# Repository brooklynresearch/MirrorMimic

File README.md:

# Mirror Mimic

This repository is for communicating and controlling robotic systems.
Currently set up for controlling torso, neck, and upper arm articulation.

## Software
1. [Arduino 1.6.8](https://www.arduino.cc)
2. [Teensyduino](https://www.pjrc.com/teensy/teensyduino.html)

### Software Libraries/Dependencies
1. DynamixelController - Controlling Dynamixels with the Teensy (Based on Arbotix Library)
2. [OSC - OSC communication with the Teensy](https://github.com/CNMAT/OSC)

## Hardware
1. [Microcontroller - Teensy 3.2](https://www.pjrc.com/store/teensy32.html)
2. [Servo - Dynamixel MX-64T](http://www.trossenrobotics.com/p/mx-64t-dynamixel-robot-actuator.aspx)
3. [Stepper Motor NEMA23 - 23L310S-LW8](http://www.anaheimautomation.com/products/stepper/stepper-motor-item.php?sID=20&pt=i&tID=75&cID=19)
4. [Stepper Driver - MBC25081TB](http://www.anaheimautomation.com/products/stepper/stepper-driver-item.php?sID=56&serID=4&pt=i&tID=87&cID=20)

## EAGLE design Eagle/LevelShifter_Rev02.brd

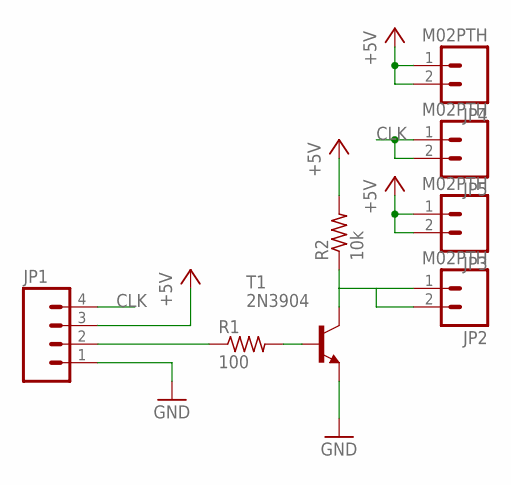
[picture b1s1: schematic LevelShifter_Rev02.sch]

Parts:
JP1: M04SCREW; SCREWTERMINAL-3.5MM-4
JP2, JP3, JP4, JP5: M02PTH; 1X02
R1: 100; 0204/7
R2: 10k; 0204/7
T1: 2N3904; TO92

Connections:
+5V: JP1.3, JP3.1, JP3.2, JP4.1, JP4.2, R2.2
CLK: JP1.4, JP5.1, JP5.2
GND: JP1.1, T1.3 (E)
unnamed: R1.2, T1.2 (B)
unnamed: JP2.1, JP2.2, R2.1, T1.1 (C)
unnamed: JP1.2, R1.1

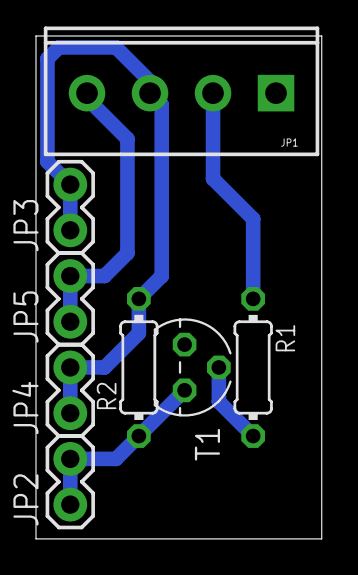
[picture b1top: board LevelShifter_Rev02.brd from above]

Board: 2 copper layers, 15.9 x 27.9 mm, 8 parts (0 on the bottom side), 6 nets.

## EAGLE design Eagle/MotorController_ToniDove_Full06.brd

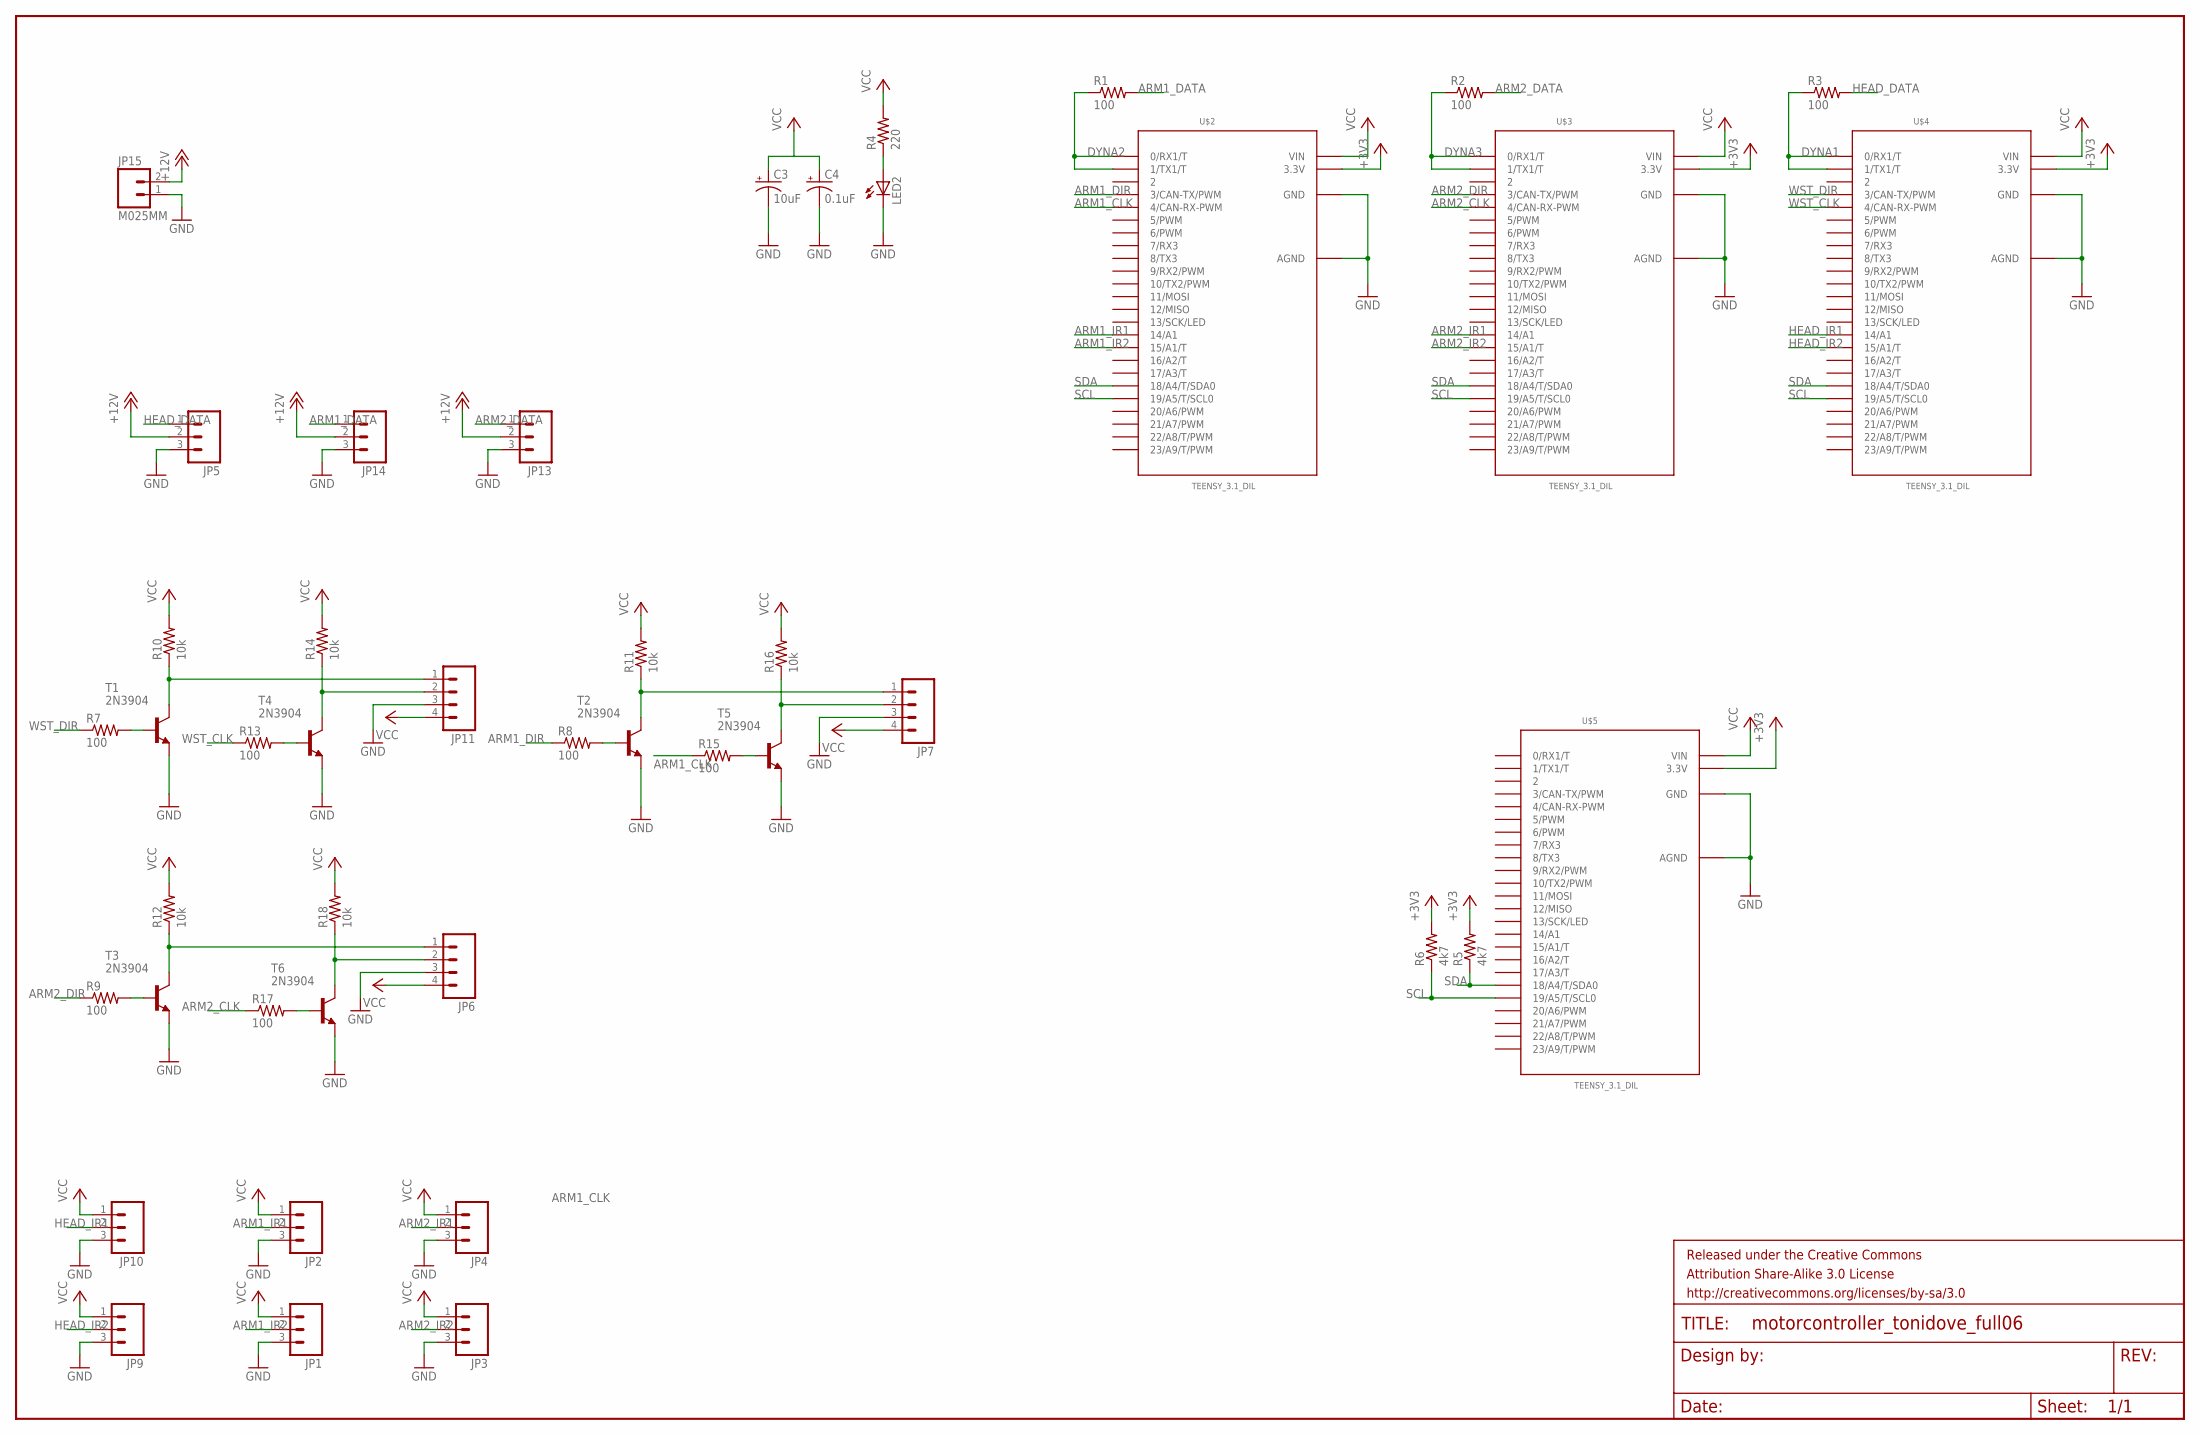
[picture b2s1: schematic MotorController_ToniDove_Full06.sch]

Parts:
C3: 10uF; E2,5-6E
C4: 0.1uF; E2,5-6E
FRAME1: FRAME-LEDGER; CREATIVE_COMMONS
JP1, JP2, JP3, JP4, JP5, JP9, JP10, JP13, JP14: M03PTH; 1X03
JP6, JP7, JP11: M04SCREW; SCREWTERMINAL-3.5MM-4
JP15: M025MM; SCREWTERMINAL-5MM-2
LED2: LED5MM
R1, R2, R3, R7, R8, R9, R13, R15, R17: 100; 0204/7
R4: 220; 0204/7
R5, R6: 4k7; 0204/7
R10, R11, R12, R14, R16, R18: 10k; 0204/7
T1, T2, T3, T4, T5, T6: 2N3904; TO92
U$2, U$3, U$4, U$5: TEENSY_3.1_DIL; TEENSY3-DIL

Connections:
+3V3: R5.2, R6.2, U$2.3.3V, U$3.3.3V, U$4.3.3V, U$5.3.3V
+12V: JP5.2, JP13.2, JP14.2, JP15.2
ARM1_CLK: R15.1, U$2.4 (4/CAN-RX-PWM)
ARM1_DATA: JP14.1, R1.2
ARM1_DIR: R8.1, U$2.3 (3/CAN-TX/PWM)
ARM1_IR1: JP2.2, U$2.14/A0 (14/A1)
ARM1_IR2: JP1.2, U$2.15/A1 (15/A1/T)
ARM2_CLK: R17.1, U$3.4 (4/CAN-RX-PWM)
ARM2_DATA: JP13.1, R2.2
ARM2_DIR: R9.1, U$3.3 (3/CAN-TX/PWM)
ARM2_IR1: JP4.2, U$3.14/A0 (14/A1)
ARM2_IR2: JP3.2, U$3.15/A1 (15/A1/T)
DYNA1: R3.1, U$4.0 (0/RX1/T), U$4.1 (1/TX1/T)
DYNA2: R1.1, U$2.0 (0/RX1/T), U$2.1 (1/TX1/T)
DYNA3: R2.1, U$3.0 (0/RX1/T), U$3.1 (1/TX1/T)
GND: C3.-, C4.-, JP1.3, JP2.3, JP3.3, JP4.3, JP5.3, JP6.3, JP7.3, JP9.3, JP10.3, JP11.3, JP13.3, JP14.3, JP15.1, LED2.K (C), T1.3 (E), T2.3 (E), T3.3 (E), T4.3 (E), T5.3 (E), T6.3 (E), U$2.AGND, U$2.GND, U$3.AGND, U$3.GND, U$4.AGND, U$4.GND, U$5.AGND, U$5.GND
HEAD_DATA: JP5.1, R3.2
HEAD_IR1: JP10.2, U$4.14/A0 (14/A1)
HEAD_IR2: JP9.2, U$4.15/A1 (15/A1/T)
unnamed: LED2.A, R4.1
unnamed: R13.2, T4.2 (B)
unnamed: R7.2, T1.2 (B)
unnamed: R8.2, T2.2 (B)
unnamed: R9.2, T3.2 (B)
unnamed: JP11.1, R10.1, T1.1 (C)
unnamed: JP7.1, R11.1, T2.1 (C)
unnamed: JP6.1, R12.1, T3.1 (C)
unnamed: JP11.2, R14.1, T4.1 (C)
unnamed: R15.2, T5.2 (B)
unnamed: JP7.2, R16.1, T5.1 (C)
unnamed: R17.2, T6.2 (B)
unnamed: JP6.2, R18.1, T6.1 (C)
SCL: R6.1, U$2.19/A5 (19/A5/T/SCL0), U$3.19/A5 (19/A5/T/SCL0), U$4.19/A5 (19/A5/T/SCL0), U$5.19/A5 (19/A5/T/SCL0)
SDA: R5.1, U$2.18/A4 (18/A4/T/SDA0), U$3.18/A4 (18/A4/T/SDA0), U$4.18/A4 (18/A4/T/SDA0), U$5.18/A4 (18/A4/T/SDA0)
VCC: C3.+, C4.+, JP1.1, JP2.1, JP3.1, JP4.1, JP6.4, JP7.4, JP9.1, JP10.1, JP11.4, R4.2, R10.2, R11.2, R12.2, R14.2, R16.2, R18.2, U$2.VIN, U$3.VIN, U$4.VIN, U$5.VIN
WST_CLK: R13.1, U$4.4 (4/CAN-RX-PWM)
WST_DIR: R7.1, U$4.3 (3/CAN-TX/PWM)

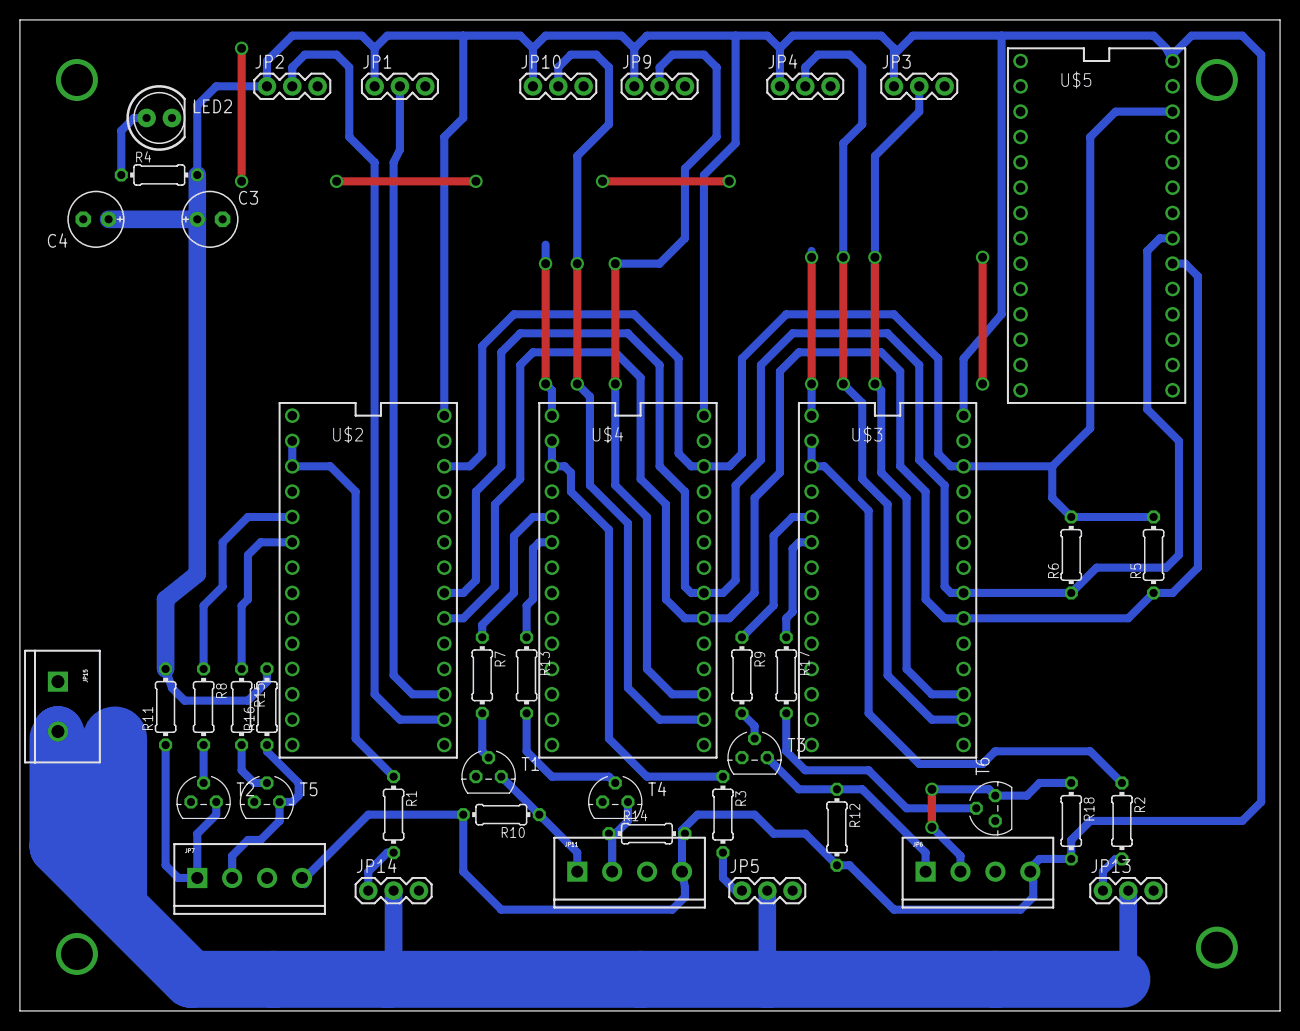
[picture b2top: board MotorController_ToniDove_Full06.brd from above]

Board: 2 copper layers, 126.3 x 99.4 mm, 45 parts (0 on the bottom side), 37 nets.

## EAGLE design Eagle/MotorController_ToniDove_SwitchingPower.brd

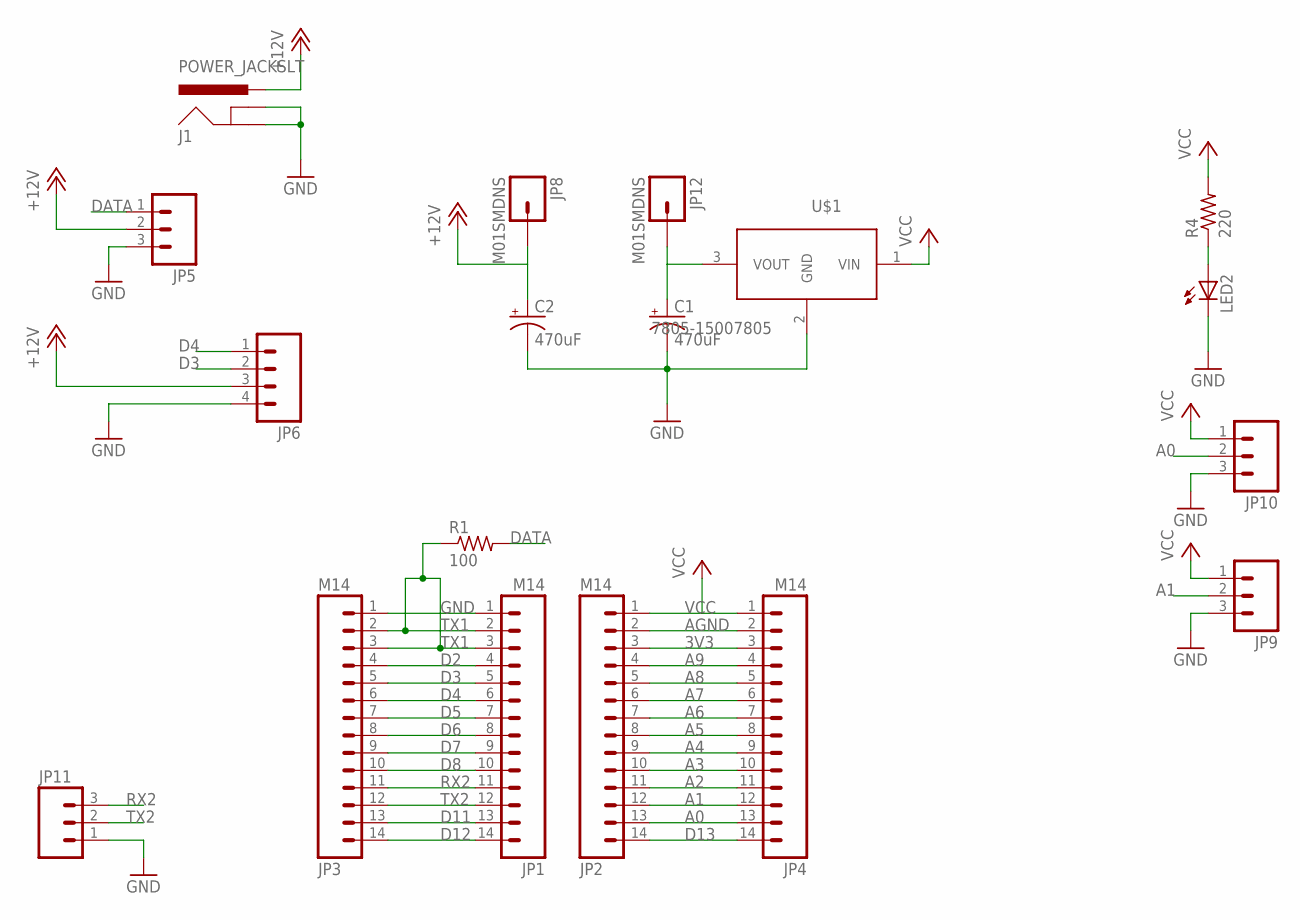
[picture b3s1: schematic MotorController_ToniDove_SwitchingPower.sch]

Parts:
C1, C2: 470uF; E5-13
J1: POWER_JACKSLT; POWER_JACK_SLOT
JP1, JP2, JP3, JP4: M14; 1X14
JP5, JP9, JP10, JP11: M03PTH; 1X03
JP6: M04PTH; 1X04
JP8, JP12: M01SMDNS; 1X01NS
LED2: LED5MM
R1: 100; 0204/7
R4: 220; 0204/7
U$1: 7805-15007805; UL94-V0

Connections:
3V3: JP2.3, JP4.3
+12V: C2.+, J1.PWR, JP5.2, JP6.3, JP8.1
A0: JP2.13, JP4.13, JP10.2
A1: JP2.12, JP4.12, JP9.2
A2: JP2.11, JP4.11
A3: JP2.10, JP4.10
A4: JP2.9, JP4.9
A5: JP2.8, JP4.8
A6: JP2.7, JP4.7
A7: JP2.6, JP4.6
A8: JP2.5, JP4.5
A9: JP2.4, JP4.4
AGND: JP2.2, JP4.2
D2: JP1.4, JP3.4
D3: JP1.5, JP3.5, JP6.2
D4: JP1.6, JP3.6, JP6.1
D5: JP1.7, JP3.7
D6: JP1.8, JP3.8
D7: JP1.9, JP3.9
D8: JP1.10, JP3.10
D11: JP1.13, JP3.13
D12: JP1.14, JP3.14
D13: JP2.14, JP4.14
DATA: JP5.1, R1.2
GND: C1.-, C2.-, J1.GND@1 (GNDBREAK), J1.GND@2 (GND), JP1.1, JP3.1, JP5.3, JP6.4, JP9.3, JP10.3, JP11.1, LED2.K (C), U$1.2 (GND)
unnamed: LED2.A, R4.1
unnamed: C1.+, JP12.1, U$1.3 (VOUT)
RX2: JP1.11, JP3.11, JP11.3
TX1: JP1.2, JP1.3, JP3.2, JP3.3, R1.1
TX2: JP1.12, JP3.12, JP11.2
VCC: JP2.1, JP4.1, JP9.1, JP10.1, R4.2, U$1.1 (VIN)

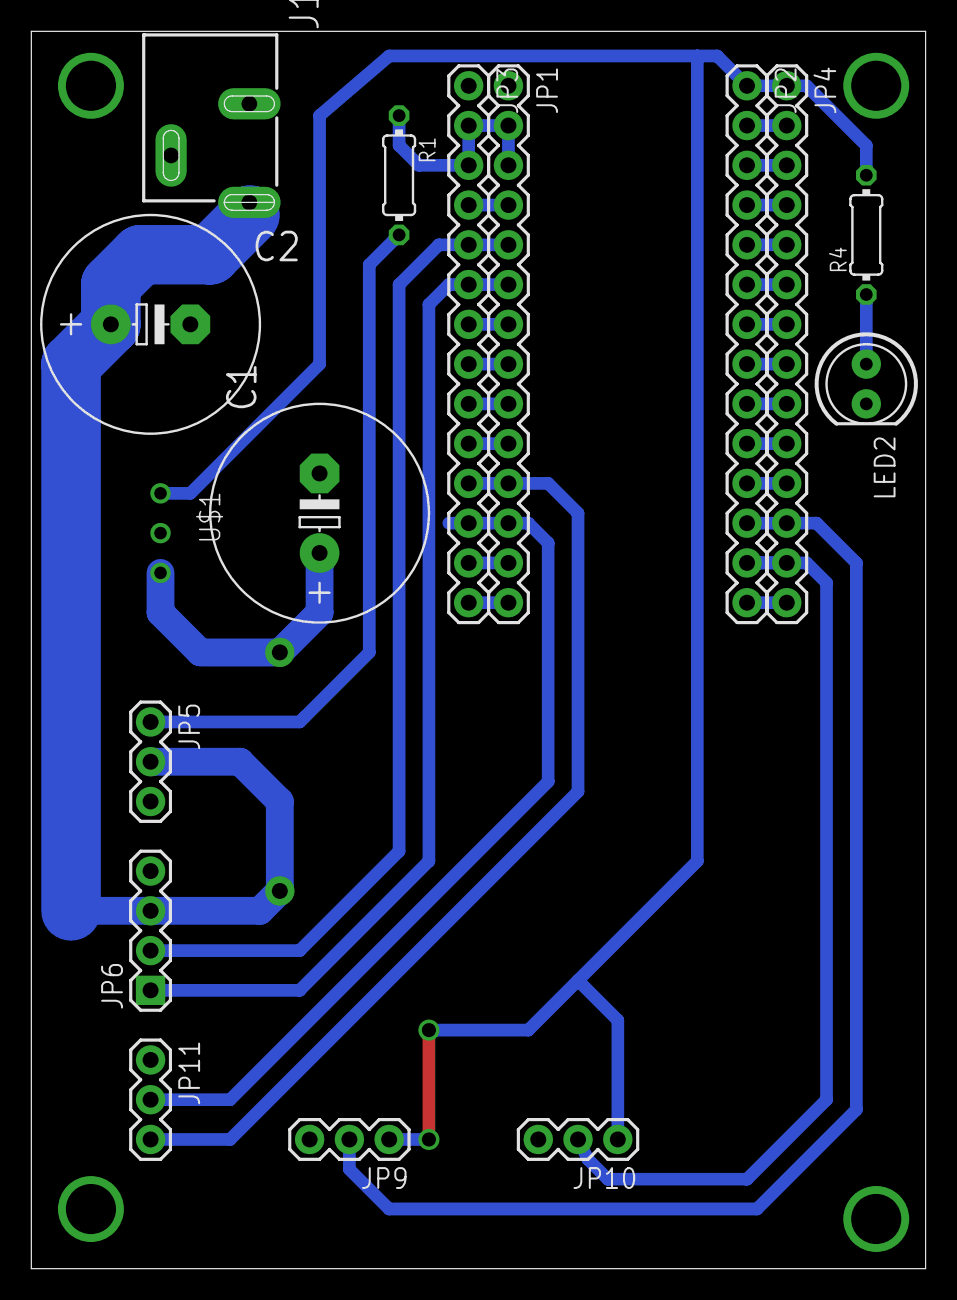
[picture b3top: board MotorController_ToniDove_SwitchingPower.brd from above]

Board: 2 copper layers, 57.1 x 79.0 mm, 18 parts (0 on the bottom side), 31 nets.

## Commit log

2016-05-06 First Commit
    Added ReadMe. Will add code soon
2016-05-06 ReadMe Fix
    Ordered list of software/hardware
2016-05-23 Uploaded Initial Teensy/Arduino Code
    Code to control Dynamixels with Teensy.
    Serial Comms, Limiters, and Feedback functions still need to be
    implemented.
2016-05-24 Streamlined Dynamixel Library
    Streamlined Dynamixel Library and added an example sketch that should
    work with Teensy 3.2 right off the bat.
2016-05-24 Serial Comms included
    Updated Arduino Code.
    Serial Comms included, Read Me updated, and incorporated new Dynamixel
    Library.
2016-05-25 OSC to serial prototype
    May need to heavily rewrite this so as to not be clunky once we have
    anything in.
    Currently just takes in OSC and has a basic commented out structure for
    how we might possibly route things. Does not currently relay serial
2016-06-09 Dynamixel Callbacks Added
    Added Callback for get AngleLimits getting Max Torque, and
    incorporating a new begin function that passes the Max Servo amount.
2016-06-09 Added Stepper Motor Control
    Added Stepper Motor Control via Serial. Need to merge Dynamixel and
    Steppermotor code into one.
2016-06-10 Consolidated Stepper and Servo Code
    Consolidated Stepper and Servo Code and added positioning commands for
    all the Servos. Need to add get commands for all positioning, torque,
    voltage, speed, etc.
2016-06-21 OSCSerial updated
    Added functionality to OSCSerial.
    Still need to send feedback of sensors and positions of motors.
2016-06-21 Minor Changes for Compiling and Checking
    OSC Serial compiles and Motor Controller lets the USB Serial know which
    address it is currently assigned to.
2016-06-22 Position Feedback
    Added Initial Position Feedback Code for both OSCSerial and Motor
    Controller code. Still needs to be fully tested.
2016-07-23 I2C Arduino Sketches And Max Tester
    Uploaded the newest Arduino sketch for Comms and Motor controller for
    the torso. Plus uploaded a basic Max Tester to test comms.
2016-08-11 Initial Push for Position Feedback
    Updated Max and Arduino sketches to get positional feedback from the
    stepper motors and servos.
2016-08-11 Quick Updates
    Max refinements

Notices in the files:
parts and their libraries:
SparkFun-Connectors: Licensing: CC v3.0 Share-Alike You are welcome to use this library for commercial purposes.
SparkFun-Aesthetics: Released under the Creative Commons Attribution Share-Alike 3.0 License
SparkFun-Aesthetics: http://creativecommons.org/licenses/by-sa/3.0
